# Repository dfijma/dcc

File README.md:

Arduino DCC+LocoNet
===================

This is heavily inspired by, though not a fork off, [DccPlusPlus](https://github.com/DccPlusPlus).

## What do we have:

- An Arduino
- A motorshield to boost logic-level DCC signals to something more beefy 
- A [FremoLNShield](http://nh-finescale.nl/fremo/dcc/fremo-ln-shield/FremoLNShield.html) to interface with Loconet

## What does it do:

The DCC sketch performs to main tasks:

 - Maintain a refresh buffer to generate a (real-time) DCC signal 
 - Proxy Loconet message to and from a host (via the serial port)

So, the sketch itself does not consitute a full DCC/Loconet command station. It needs to be complemented with a host application that does the heavy lifting (user interface, actual processing of Loconet messages, or even more intelligent control). Such a host application would

  - receive Loconet messages proxied by the DCC sketch, for example to detect sensor events
  - send Loconet messages trough the DCC sketch, for example to control switches
  - update slots in the refresh buffer to control the DCC signal send to the loco's on the track

That would make a basic DCC/Loconet control station. A java based host application "in progress" is included. It combines a funny eighties "TUI" interface with a contempary Model-View-Controller architecture:

There is also some experimental Python code for a Raspberry-based host application. Though this is still based on an older version of the Arduino sketch that used I2C instead of serial communication. It would be fun to revive this, as it could use all kind of LCD displays and rotary encoders to create something that actually looks like a command station. The Raspberry is on my setup, but not fully functional at the moment:

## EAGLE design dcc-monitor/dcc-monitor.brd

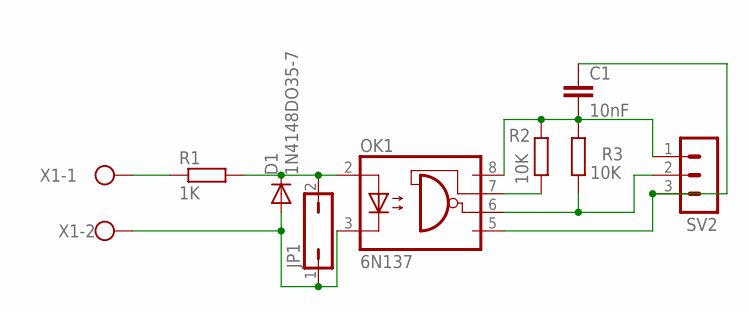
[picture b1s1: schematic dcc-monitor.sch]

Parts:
C1: 10nF; C025-025X050
D1: 1N4148DO35-7; DO35-7
JP1: JP1Q; JP1
OK1: 6N137; DIL08
R1: 1K; 0309/12
R2, R3: 10K; 0309/12
SV2: MA03-1
X1: W237-102

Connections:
unnamed: C1.1, OK1.5 (GND), SV2.3
unnamed: OK1.7 (VE), R2.1
unnamed: OK1.6 (VO), R3.1, SV2.2
unnamed: D1.A, JP1.1, OK1.3 (C), X1.2
unnamed: D1.C, JP1.2, OK1.2 (A), R1.2
unnamed: R1.1, X1.1
unnamed: C1.2, OK1.8 (VCC), R2.2, R3.2, SV2.1

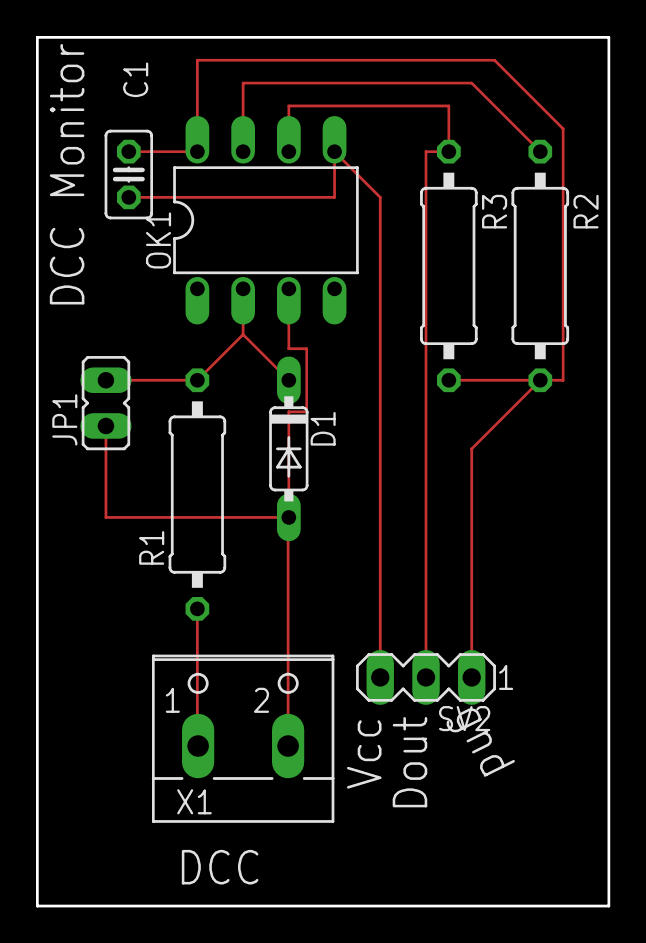
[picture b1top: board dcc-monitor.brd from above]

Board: 2 copper layers, 31.8 x 48.3 mm, 9 parts (0 on the bottom side), 7 nets.

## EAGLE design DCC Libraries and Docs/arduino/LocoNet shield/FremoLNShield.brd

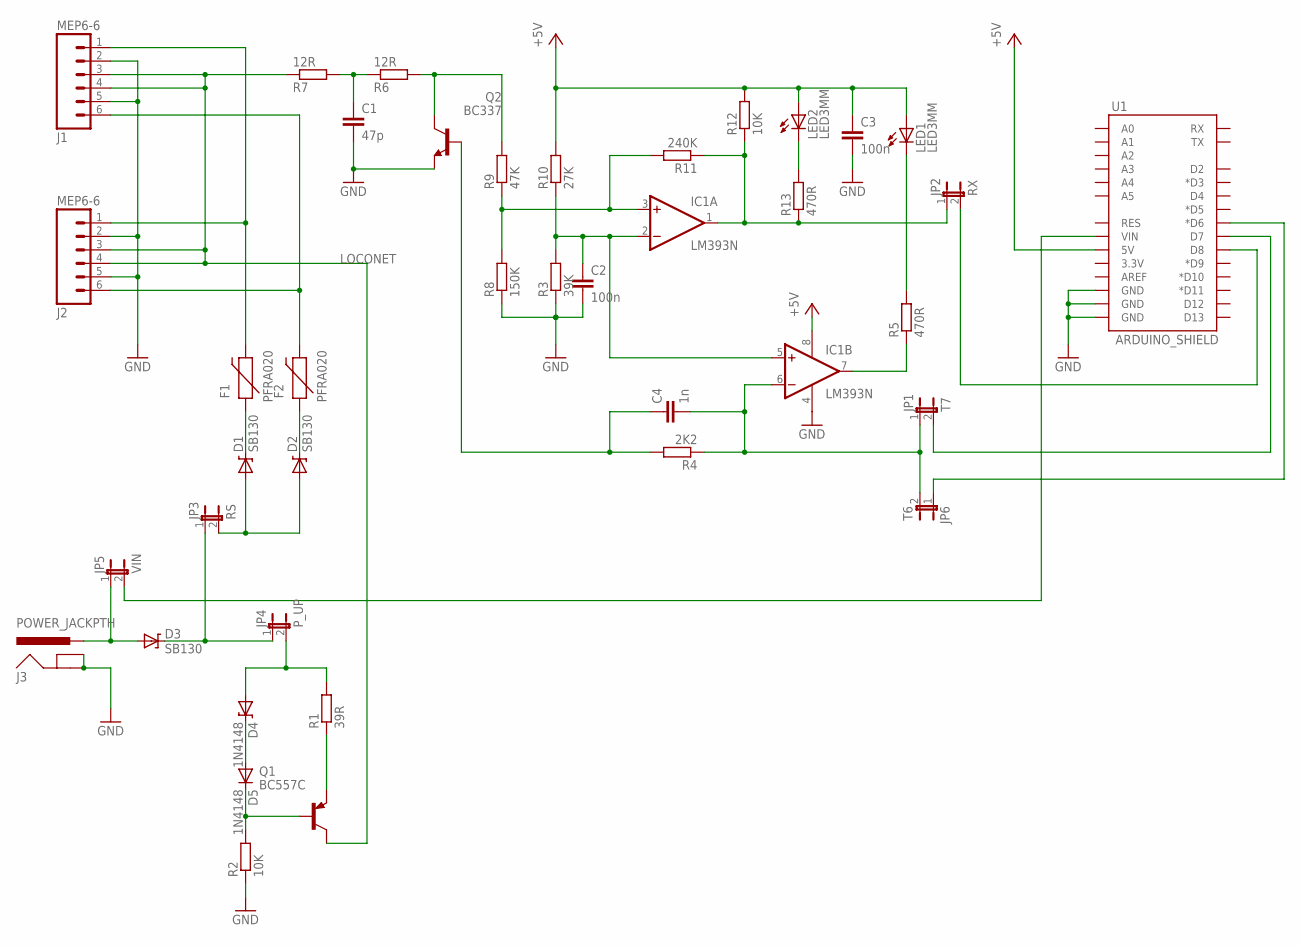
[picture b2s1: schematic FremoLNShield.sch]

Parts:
C1: 47p; C025-025X050
C2, C3: 100n; C025-025X050
C4: 1n; C025-025X050
D1, D2, D3: SB130; DIODE-ZENER
D4: 1N4148; DIODE-ZENER
D5: 1N4148; DO35-10
F1, F2: PFRA020; PTC
IC1: LM393N; DIL08
J1, J2: MEP6-6; RJ11-6
J3: POWER_JACKPTH; POWER_JACK_PTH
JP1: T7; 1X02
JP2: RX; 1X02
JP3: RS; 1X02
JP4: P_UP; 1X02
JP5: VIN; 1X02
JP6: T6; 1X02
LED1, LED2: LED3MM; PFEIL3_LED3MM
Q1: BC557C; TO92
Q2: BC337; TO92
R1: 39R; 0207/10
R2, R12: 10K; 0207/10
R3: 39K; 0207/10
R4: 2K2; 0207/10
R5, R13: 470R; 0207/10
R6, R7: 12R; 0207/10
R8: 150K; 0207/10
R9: 47K; 0207/10
R10: 27K; 0207/10
R11: 240K; 0207/10
U1: ARDUINO_SHIELD; DUEMILANOVE_SHIELD

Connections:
GND: C1.2, C2.2, C3.2, IC1.4 (V-), J1.2, J1.5, J2.2, J2.5, J3.GND, J3.GNDBREAK, Q2.1 (E), R2.1, R3.1, R8.1, U1.GND@0 (GND), U1.GND@1 (GND), U1.GND@2 (GND)
LN_RX: IC1.1 (OUT), JP2.1, R11.1, R12.1, R13.1
LN_TX: C4.2, IC1.6 (-IN), JP1.1, JP6.2, R4.1
LOCONET: J1.3, J1.4, J2.3, J2.4, Q1.3 (C), R7.1
unnamed: D3.P$2 (A), J3.PWR, JP5.1
unnamed: D3.P$1 (C), JP3.1, JP4.1
unnamed: D1.P$1 (C), F1.P$1 (1)
unnamed: D2.P$1 (C), F2.P$1 (1)
unnamed: F1.P$2 (2), J1.1, J2.1
unnamed: D4.P$2 (A), JP4.2, R1.2
unnamed: F2.P$2 (2), J1.6, J2.6
unnamed: D4.P$1 (C), D5.A
unnamed: D5.C, Q1.2 (B), R2.2
unnamed: C2.1, IC1.2 (-IN), IC1.5 (+IN), R3.2, R10.1
unnamed: Q1.1 (E), R1.1
unnamed: C4.1, Q2.2 (B), R4.2
unnamed: C1.1, R6.1, R7.2
unnamed: D1.P$2 (A), D2.P$2 (A), JP3.2
unnamed: JP2.2, U1.D8
unnamed: Q2.3 (C), R6.2, R9.2
unnamed: IC1.3 (+IN), R8.2, R9.1, R11.2
unnamed: JP1.2, U1.D7
unnamed: IC1.7 (OUT), R5.1
unnamed: LED2.K (C), R13.2
unnamed: LED1.K (C), R5.2
unnamed: JP6.1, U1.D6 (*D6)
VCC: C3.1, IC1.8 (V+), LED1.A, LED2.A, R10.2, R12.2, U1.5V
VIN: JP5.2, U1.VIN

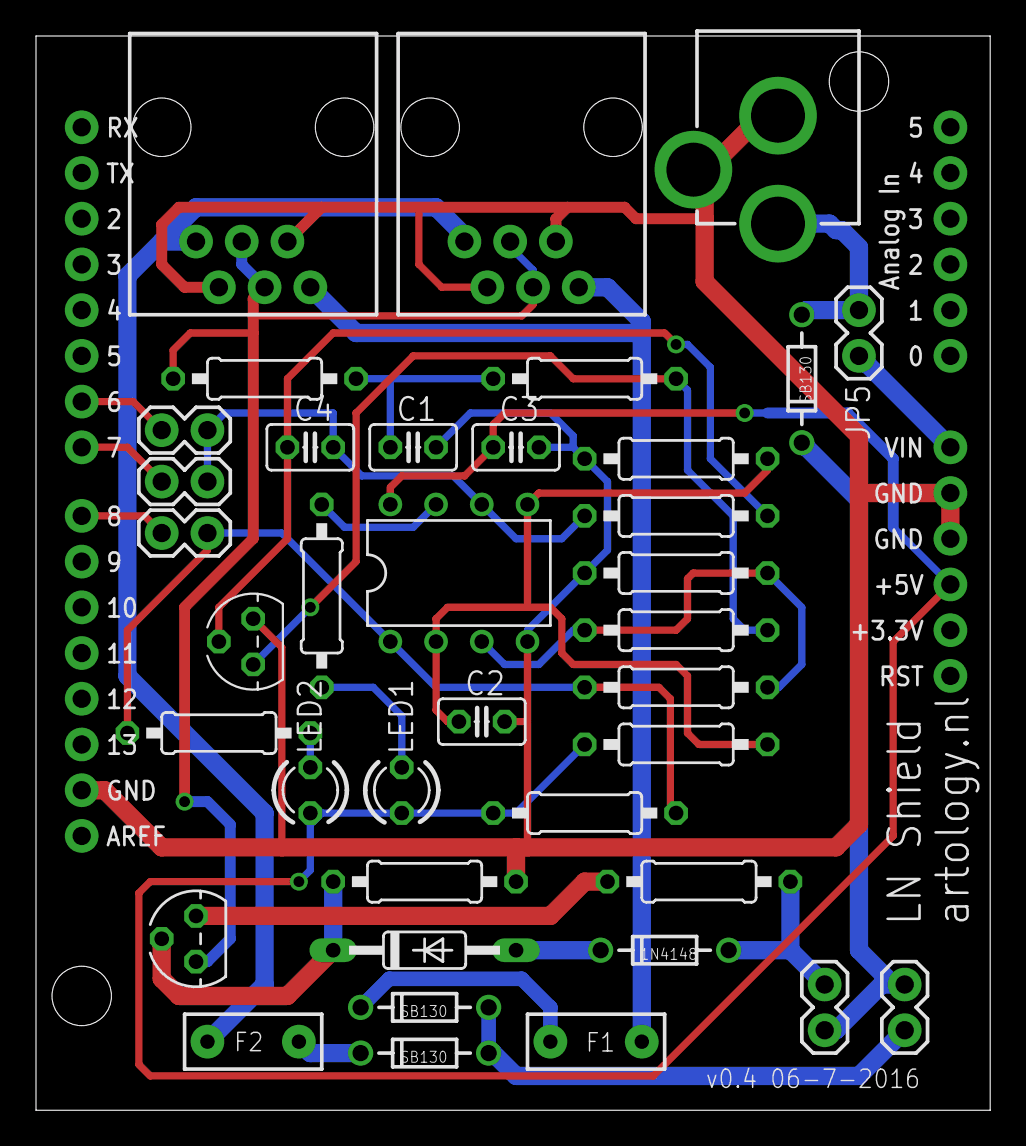
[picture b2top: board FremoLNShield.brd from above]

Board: 2 copper layers, 53.0 x 59.7 mm, 39 parts (0 on the bottom side), 28 nets.

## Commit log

2017-08-09 the ardino sketches for the DCC signal generator
2017-08-10 first version with direct use of timers
2017-08-10 initial version of the raspberry pi side
2017-08-11 actual square waves (2 channels) on a scope!
2017-08-11 polish the comments
2017-08-24 train actually runs
2017-09-01 class for rotary switch plus a test program
2017-10-17 multiple refesh slots and current detection
2017-10-17 short description of state machine handling rotary switch, plus initial implementation
2017-10-17 improve my rotational state machine
2017-10-17 no pullup, BOTH edges
2017-10-17 glue my new rotary encode to actual GPIO pins
2017-10-17 small correction; after debugging against actual hardware
2017-10-17 some comment
2017-10-17 rename
2018-01-16 cleanup a bit
2018-01-18 WIP: use timer0 and timer2 (freeing up timer1)
2018-01-18 WIP: integrate LocoNet monitor
2018-01-28 Driving works, headlights don't
2018-05-21 tweak test_rotary
2018-05-21 toy around with SMBus
2018-05-21 try keypad
2018-06-06 commit some untracked files floating around
2018-06-06 play around with rotary a bit
2018-09-29 starting cleaner DCC version
2018-10-27 serial PC to sniff Loconet
2018-10-27 schematics and board for DCC Monitor
2018-10-27 some test python to talk i2c
2018-10-27 just echo some i2c
2018-10-27 try to echo loconet through i2c
2018-10-27 echo loconet through serial
2018-10-27 my DCC monitor
2018-10-27 WIP on control station
2018-10-29 create MVC TUI
2018-10-29 remove old Arduino test thingy
2018-10-29 Remove old Wire 'hello world' example
2018-10-29 remove old I2C Arduino example
2018-10-29 remove experimental attempt to bride LocoNet<>I2C
2018-10-29 archive some old arduino stuff
2018-10-29 happy hacking on java serial client
2018-10-29 some more new classes for java serial client
2018-10-29 first attempt to integrate DCC+LocoNet+Serial
2018-10-30 change S parser
2018-10-30 tweak arduino line protocol a bit
2018-10-30 messages, and show decoded LocoNet packages
2018-10-31 it works!
2018-11-03 refactor the line interface a bit
2018-11-03 make listening to serial thread safe
2018-11-04 switch off should indeed switch off
2018-11-04 sensors work
2018-11-04 java8
2018-11-07 repair unit test
2018-11-07 cleanup tree a bit
2018-11-07 add a README.md
2018-11-07 OK, some pictures
2018-11-11 use a more portable serial port lib, it actually runs on Raspberry PI
2019-03-13 use mvc library
2019-03-13 correct run.sh
2019-03-14 resolve some sonarcube warnings; mock serial so that unit test works
2019-03-14 main view creates throttle views itself
2022-09-10 some stuff
2026-04-05 FIXME and some documentation

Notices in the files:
parts and their libraries:
SparkFun-DiscreteSemi: Licensing: CC v3.0 Share-Alike You are welcome to use this library for commercial purposes.
